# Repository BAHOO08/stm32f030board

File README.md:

It is simple board with tms320f030.
it is not tested now.
The board looks like this.

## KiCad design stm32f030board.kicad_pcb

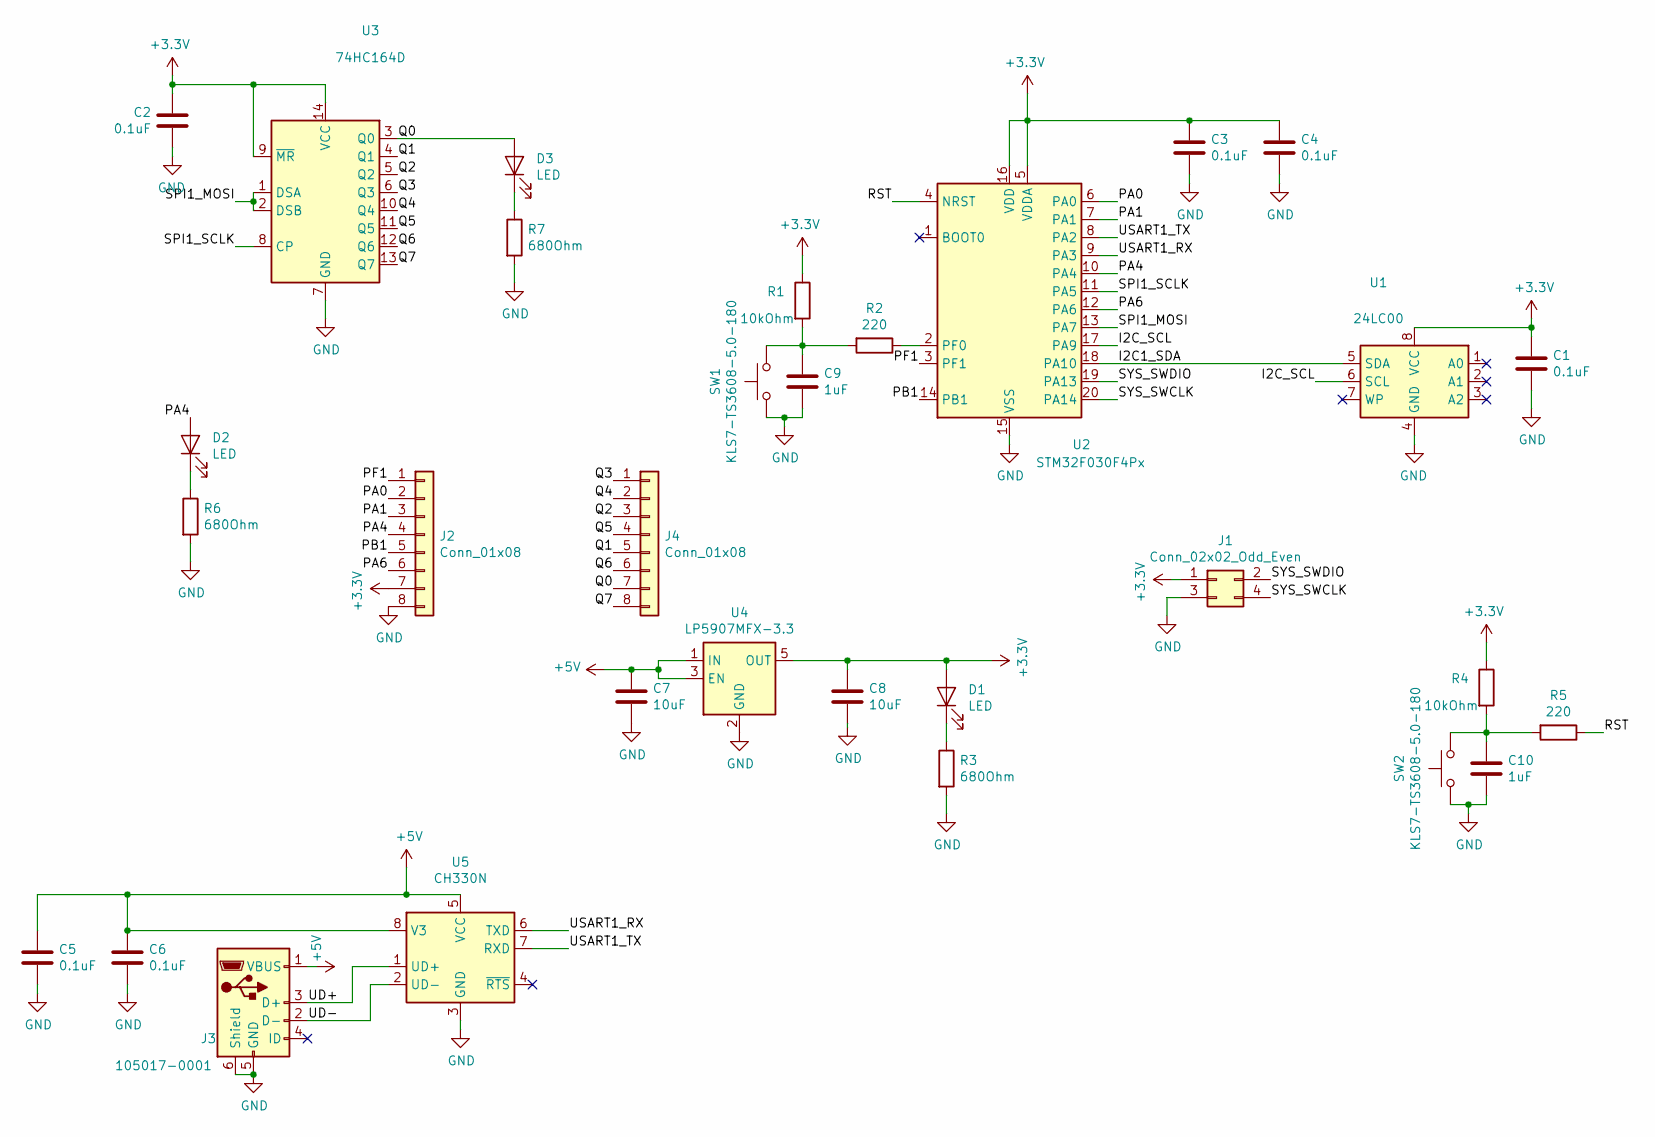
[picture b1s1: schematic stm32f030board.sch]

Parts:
C1, C2, C3, C4, C5, C6: 0.1uF; C_0805_2012Metric
C7, C8: 10uF; C_0805_2012Metric
C9, C10: 1uF; C_0805_2012Metric
D1, D2, D3: LED; LED_0603_1608Metric
J1: Conn_02x02_Odd_Even; PinSocket_2x02_P2.54mm_Horizontal
J2, J4: Conn_01x08; PinHeader_1x08_P2.54mm_Vertical
J3: 105017-0001; USB_Micro-B_Molex-105017-0001
R1, R4: 10kOhm; R_0805_2012Metric
R2, R5: 220; R_0805_2012Metric
R3, R6, R7: 680Ohm; R_0805_2012Metric
SW1, SW2: KLS7-TS3608-5.0-180; SW_Push_SPST_NO_Alps_SKRK
U1: 24LC00; SOIC-8_3.9x4.9mm_P1.27mm
U2: STM32F030F4Px; TSSOP-20_4.4x6.5mm_P0.65mm
U3: 74HC164D; SOIC-14_3.9x8.7mm_P1.27mm
U4: LP5907MFX-3.3; SOT-23-5
U5: CH330N; SOIC-8_3.9x4.9mm_P1.27mm

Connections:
+3V3: C1.1, C2.1, C3.1, C4.1, C8.1, D1.2 (A), J1.1, J2.7, R1.1, R4.1, U1.8 (VCC), U2.5 (VDDA), U2.16 (VDD), U3.9 (~MR), U3.14 (VCC), U4.5 (OUT)
+5V: C5.1, C6.1, C7.1, J3.1 (VBUS), U4.1 (IN), U4.3 (EN), U5.5 (VCC), U5.8 (V3)
/I2C1_SDA: U1.5 (SDA), U2.18 (PA10)
/I2C_SCL: U1.6 (SCL), U2.17 (PA9)
/PA0: J2.2, U2.6 (PA0)
/PA1: J2.3, U2.7 (PA1)
/PA4: D2.2 (A), J2.4, U2.10 (PA4)
/PA6: J2.6, U2.12 (PA6)
/PB1: J2.5, U2.14 (PB1)
/PF1: J2.1, U2.3 (PF1)
/Q0: D3.2 (A), J4.7, U3.3 (Q0)
/Q1: J4.5, U3.4 (Q1)
/Q2: J4.3, U3.5 (Q2)
/Q3: J4.1, U3.6 (Q3)
/Q4: J4.2, U3.10 (Q4)
/Q5: J4.4, U3.11 (Q5)
/Q6: J4.6, U3.12 (Q6)
/Q7: J4.8, U3.13 (Q7)
/RST: R5.1, U2.4 (NRST)
/SPI1_MOSI: U2.13 (PA7), U3.1 (DSA), U3.2 (DSB)
/SPI1_SCLK: U2.11 (PA5), U3.8 (CP)
/SYS_SWCLK: J1.4, U2.20 (PA14)
/SYS_SWDIO: J1.2, U2.19 (PA13)
/UD+: J3.3 (D+), U5.1 (UD+)
/UD-: J3.2 (D-), U5.2 (UD-)
/USART1_RX: U2.9 (PA3), U5.6 (TXD)
/USART1_TX: U2.8 (PA2), U5.7 (RXD)
GND: C1.2, C2.2, C3.2, C4.2, C5.2, C6.2, C7.2, C8.2, C9.2, C10.2, J1.3, J2.8, J3.5 (GND), J3.6 (Shield), R3.2, R6.2, R7.2, SW1.1, SW2.1, U1.4 (GND), U2.15 (VSS), U3.7 (GND), U4.2 (GND), U5.3 (GND)
unnamed: C9.1, R1.2, R2.2, SW1.2
unnamed: C10.1, R4.2, R5.2, SW2.2
unnamed: D1.1 (K), R3.1
unnamed: D2.1 (K), R6.1
unnamed: D3.1 (K), R7.1
unnamed: R2.1, U2.2 (PF0)

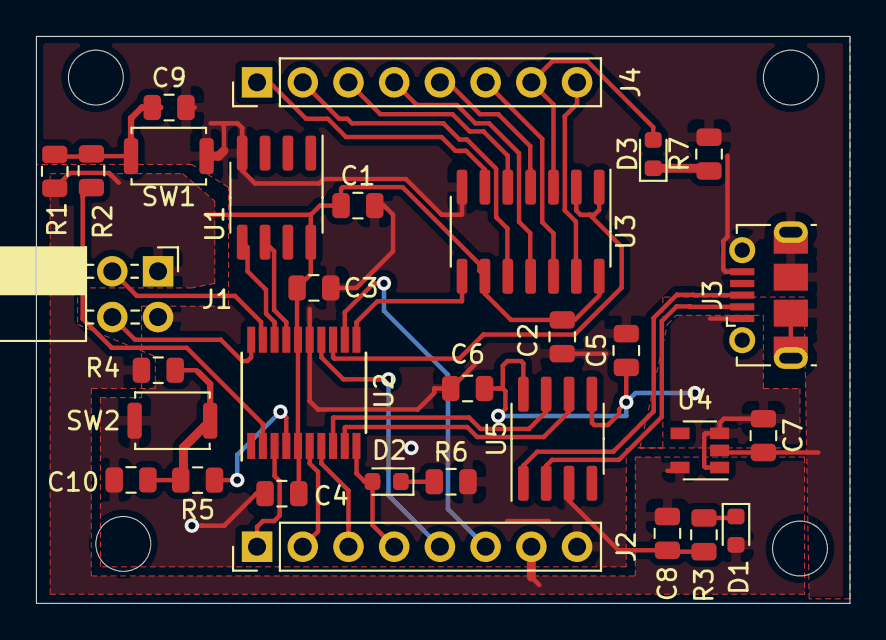
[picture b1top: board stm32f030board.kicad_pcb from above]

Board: 2 copper layers, 45.2 x 31.5 mm, 31 parts (0 on the bottom side), 34 nets.

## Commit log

2020-08-23 Version with more holes
2020-08-23 ver with smal through hole
2020-08-29 release v1.2
